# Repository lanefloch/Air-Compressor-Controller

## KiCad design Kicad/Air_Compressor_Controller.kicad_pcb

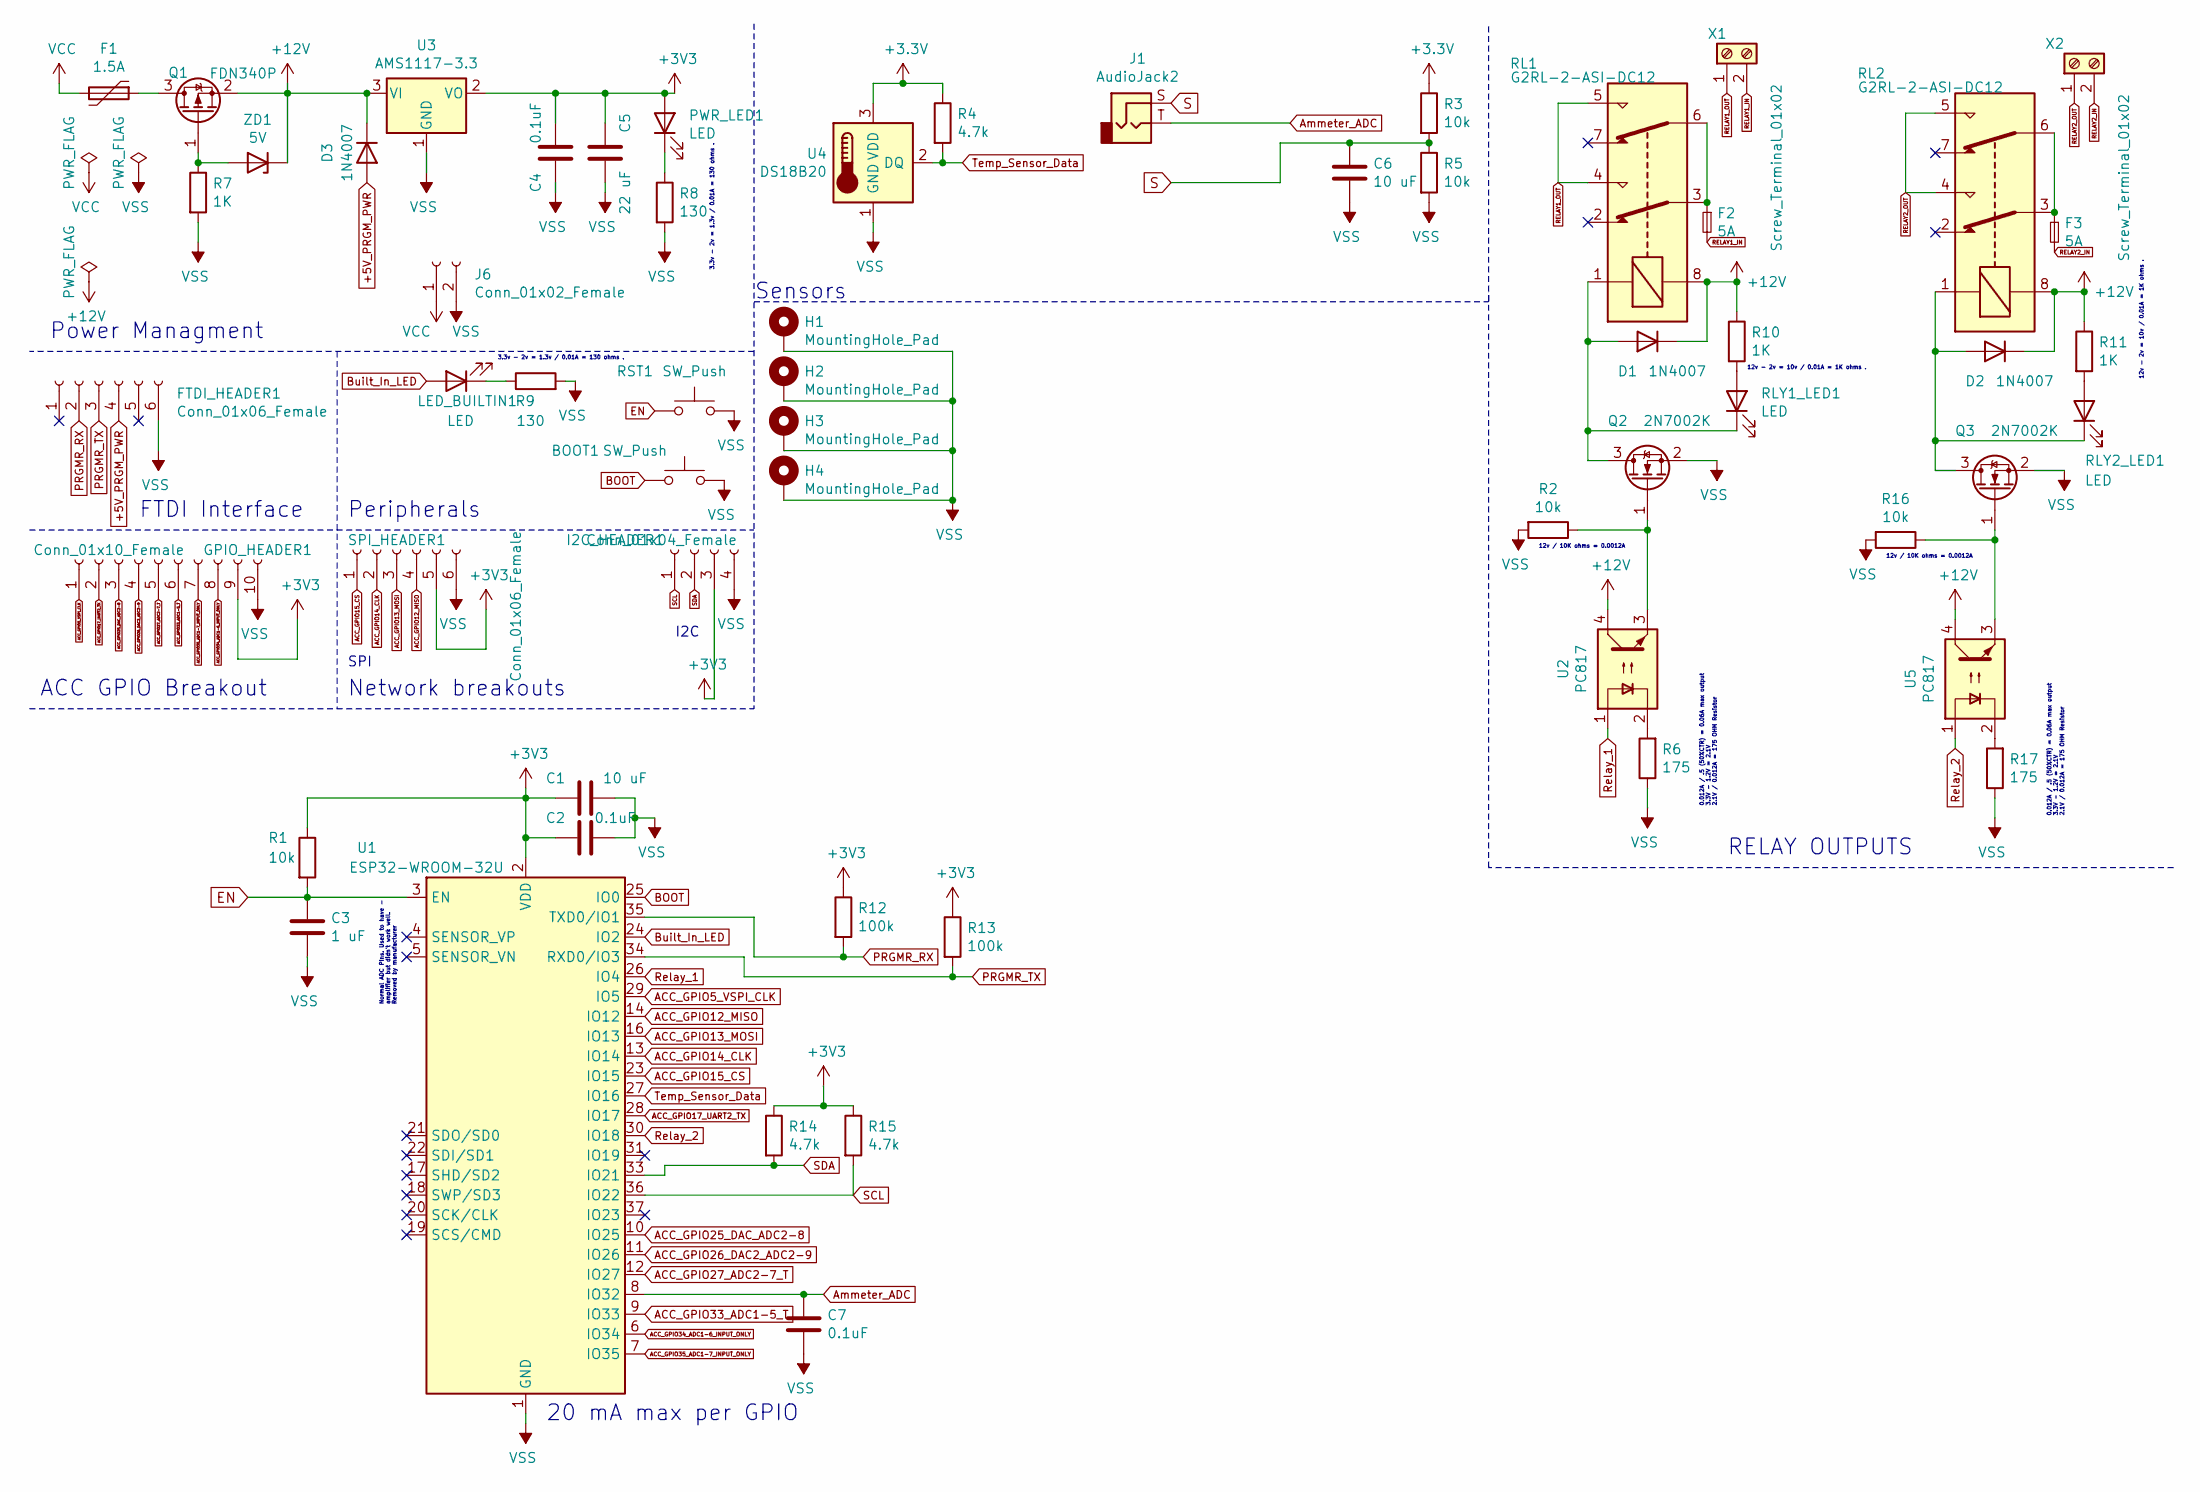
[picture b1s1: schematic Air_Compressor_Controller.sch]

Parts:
BOOT1: SW_Push; SW_SPST_PTS645; LCSC C271750
C1, C6: 10 uF; C_1206_3216Metric_Pad1.33x1.80mm_HandSolder; LCSC C14860
C2, C4, C7: 0.1uF; C_1206_3216Metric_Pad1.33x1.80mm_HandSolder; LCSC C24497
C3: 1 uF; C_1206_3216Metric_Pad1.33x1.80mm_HandSolder; LCSC C1848
C5: 22 uF; C_1206_3216Metric_Pad1.33x1.80mm_HandSolder; LCSC C90146
D1, D2, D3: 1N4007; D_1206_3216Metric_Pad1.42x1.75mm_HandSolder; LCSC C108803
F1: 1.5A; Fuse_1206_3216Metric_Pad1.42x1.75mm_HandSolder; LCSC C883133
F2, F3: 5A; Fuseholder_Cylinder-5x20mm_Stelvio-Kontek_PTF78_Horizontal_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; LCSC C58066
FTDI_HEADER1: Conn_01x06_Female; PinHeader_1x06_P2.54mm_Vertical; LCSC C40877
GPIO_HEADER1: Conn_01x10_Female; PinHeader_1x10_P2.54mm_Vertical; LCSC C35445
H1, H2, H3, H4: MountingHole_Pad; MountingHole_3.2mm_M3_Pad_Via; LCSC N/A
I2C_HEADER1: Conn_01x04_Female; PinHeader_1x04_P2.54mm_Vertical; LCSC C2718488
J1: AudioJack2; Jack_3.5mm_PJ320D_Horizontal; LCSC C521460
J6: Conn_01x02_Female; PinHeader_1x02_P2.54mm_Vertical; LCSC N/A
LED_BUILTIN1: LED; LED_0805_2012Metric_Pad1.15x1.40mm_HandSolder; LCSC C72037
PWR_LED1: LED; LED_0805_2012Metric_Pad1.15x1.40mm_HandSolder; LCSC C72037
Q1: FDN340P; SOT-23; LCSC C2890122
Q2, Q3: 2N7002K; SOT-23; LCSC C38161
R1, R2, R3, R5, R16: 10k; R_1206_3216Metric_Pad1.30x1.75mm_HandSolder; LCSC C140407
R4, R14, R15: 4.7k; R_1206_3216Metric_Pad1.30x1.75mm_HandSolder; LCSC C17936
R6, R17: 175; R_1206_3216Metric_Pad1.30x1.75mm_HandSolder; LCSC C322897
R7, R10, R11: 1K; R_1206_3216Metric_Pad1.30x1.75mm_HandSolder; LCSC C1469
R8, R9: 130; R_1206_3216Metric_Pad1.30x1.75mm_HandSolder; LCSC C17914
R12, R13: 100k; R_1206_3216Metric_Pad1.30x1.75mm_HandSolder; LCSC C118849
RL1, RL2: G2RL-2-ASI-DC12; Relay_DPDT_Omron_G2RL; LCSC C61458
RLY1_LED1, RLY2_LED1: LED; LED_0805_2012Metric_Pad1.15x1.40mm_HandSolder; LCSC C72037
RST1: SW_Push; SW_SPST_PTS645; LCSC C271750
SPI_HEADER1: Conn_01x06_Female; PinHeader_1x06_P2.54mm_Vertical; LCSC C40877
U1: ESP32-WROOM-32U; LCSC C328062
U2, U5: PC817; DIP-4_W7.62mm; LCSC C390734
U3: AMS1117-3.3; SOT-223-3_TabPin2; LCSC C347222
U4: DS18B20; TO-92_Inline; LCSC C376006
X1, X2: Screw_Terminal_01x02; TerminalBlock_Phoenix_MKDS-1,5-2_1x02_P5.00mm_Horizontal; LCSC N/A
ZD1: 5V; D_SOD-323_HandSoldering; LCSC C22612

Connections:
+5V_PRGM_PWR: D3.2 (A), FTDI_HEADER1.4
+12V: D1.1 (K), D2.1 (K), D3.1 (K), Q1.2 (S), R10.1, R11.1, RL1.8, RL2.8, U2.4, U3.3 (VI), U5.4, ZD1.1 (K)
ACC_GPIO5_VSPI_CLK: GPIO_HEADER1.1, U1.29 (IO5)
ACC_GPIO12_MISO: SPI_HEADER1.4, U1.14 (IO12)
ACC_GPIO13_MOSI: SPI_HEADER1.3, U1.16 (IO13)
ACC_GPIO14_CLK: SPI_HEADER1.2, U1.13 (IO14)
ACC_GPIO15_CS: SPI_HEADER1.1, U1.23 (IO15)
ACC_GPIO17_UART2_TX: GPIO_HEADER1.2, U1.28 (IO17)
ACC_GPIO25_DAC_ADC2-8: GPIO_HEADER1.3, U1.10 (IO25)
ACC_GPIO26_DAC2_ADC2-9: GPIO_HEADER1.4, U1.11 (IO26)
ACC_GPIO27_ADC2-7_T: GPIO_HEADER1.5, U1.12 (IO27)
ACC_GPIO33_ADC1-5_T: GPIO_HEADER1.6, U1.9 (IO33)
ACC_GPIO34_ADC1-6_INPUT_ONLY: GPIO_HEADER1.8, U1.6 (IO34)
ACC_GPIO35_ADC1-7_INPUT_ONLY: GPIO_HEADER1.7, U1.7 (IO35)
Ammeter_ADC: C7.1, J1.T, U1.8 (IO32); also elsewhere on the board
BOOT: BOOT1.1, U1.25 (IO0)
Built_In_LED: LED_BUILTIN1.2 (A), U1.24 (IO2)
EN: C3.1, R1.2, RST1.1, U1.3 (EN)
unnamed: D1.2 (A), Q2.3 (D), RL1.1, RLY1_LED1.1 (K)
unnamed: D2.2 (A), Q3.3 (D), RL2.1, RLY2_LED1.1 (K)
unnamed: F1.1, Q1.3 (D)
unnamed: F2.1, RL1.3, RL1.6
unnamed: F3.1, RL2.3, RL2.6
unnamed: LED_BUILTIN1.1 (K), R9.1
unnamed: PWR_LED1.1 (K), R8.1
unnamed: Q1.1 (G), R7.1, ZD1.2 (A)
unnamed: Q2.1 (G), R2.1, U2.3
unnamed: Q3.1 (G), R16.1, U5.3
unnamed: R6.2, U2.2
unnamed: R10.2, RLY1_LED1.2 (A)
unnamed: R11.2, RLY2_LED1.2 (A)
unnamed: R17.2, U5.2
PRGMR_RX: FTDI_HEADER1.2, R12.2, U1.35 (TXD0/IO1)
PRGMR_TX: FTDI_HEADER1.3, R13.2, U1.34 (RXD0/IO3)
RELAY1_IN: F2.2, X1.2
RELAY1_OUT: RL1.4, RL1.5, X1.1
RELAY2_IN: F3.2, X2.2
RELAY2_OUT: RL2.4, RL2.5, X2.1
Relay_1: U1.26 (IO4), U2.1
Relay_2: U1.30 (IO18), U5.1
S: C6.1, J1.S, R3.2, R5.1; also elsewhere on the board
SCL: I2C_HEADER1.1, R15.2, U1.36 (IO22)
SDA: I2C_HEADER1.2, R14.2, U1.33 (IO21)
Temp_Sensor_Data: R4.2, U1.27 (IO16), U4.2 (DQ)
VCC: F1.2, J6.1
VSS: BOOT1.2, C1.1, C2.1, C3.2, C4.2, C5.1, C6.2, C7.2, FTDI_HEADER1.6, GPIO_HEADER1.10, H1.1, H2.1, H3.1, H4.1, I2C_HEADER1.4, J6.2, Q2.2 (S), Q3.2 (S), R2.2, R5.2, R6.1, R7.2, R8.2, R9.2, R16.2, R17.1, RST1.2, SPI_HEADER1.6, U1.1 (GND), U1.15 (GND), U1.38 (GND), U1.39 (GND), U3.1 (GND), U4.1 (GND)

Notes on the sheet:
12v / 10K ohms = 0.0012A
0.012A / .5 (50%CTR) = 0.06A max output 3.3V - 1.2V = 2.1V 2.1V / 0.012A = 175 OHM Resistor
Power Managment
FTDI Interface
Peripherals
3.3v - 2v = 1.3v / 0.01A = 130 ohms .
Normal ADC Pins. Used to have - amplifier but didn't work well. Removed by manufacturer
20 mA max per GPIO
Network breakouts
SPI
I2C
ACC GPIO Breakout
Sensors
12v - 2v = 10v / 0.01A = 1K ohms .
RELAY OUTPUTS

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
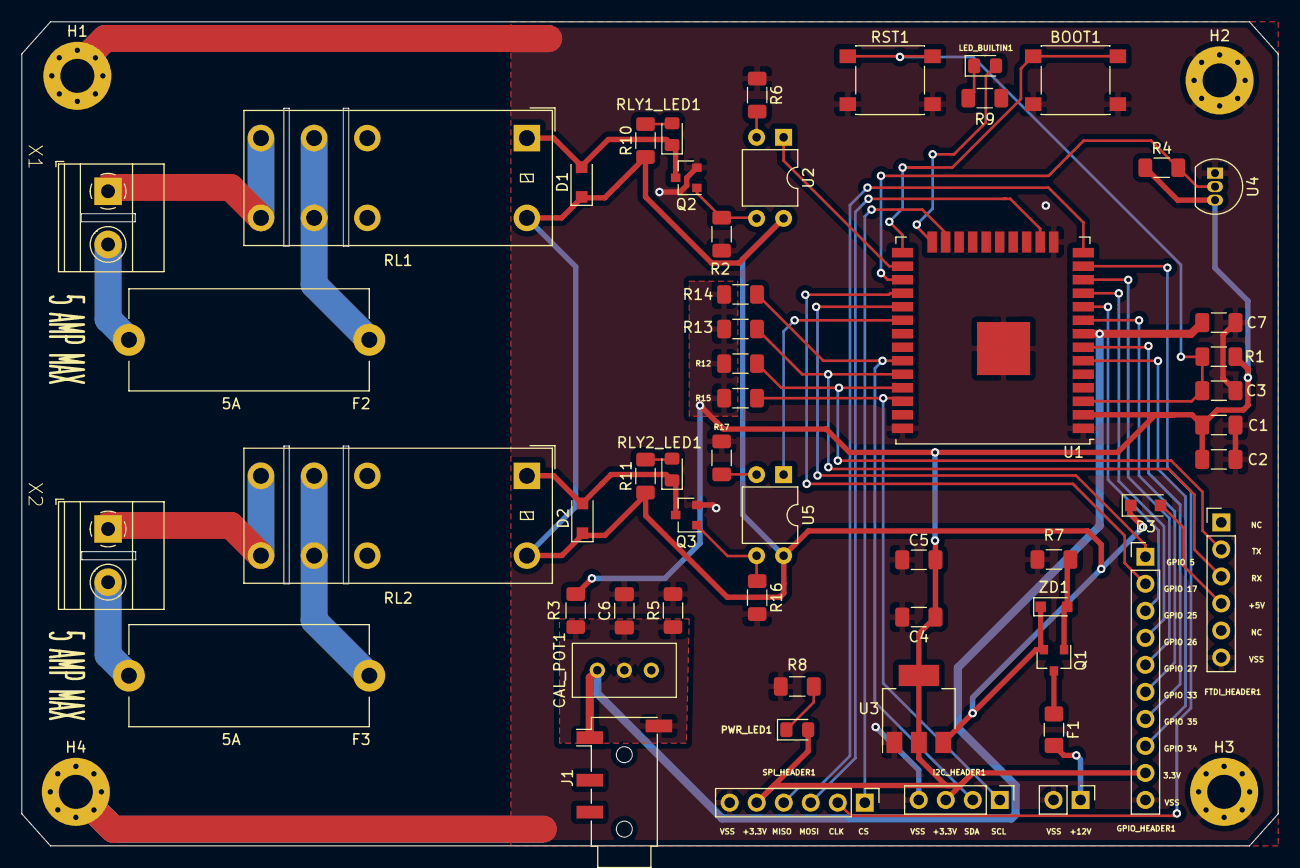
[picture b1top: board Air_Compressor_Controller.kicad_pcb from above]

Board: 2 copper layers, 118.1 x 77.5 mm, 60 parts (0 on the bottom side), 47 nets.

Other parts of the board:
CAL_POT1: 5k; Potentiometer_Bourns_3296W_Vertical

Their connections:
Ammeter_ADC: CAL_POT1.3; also elsewhere on the board
S: CAL_POT1.2; also elsewhere on the board

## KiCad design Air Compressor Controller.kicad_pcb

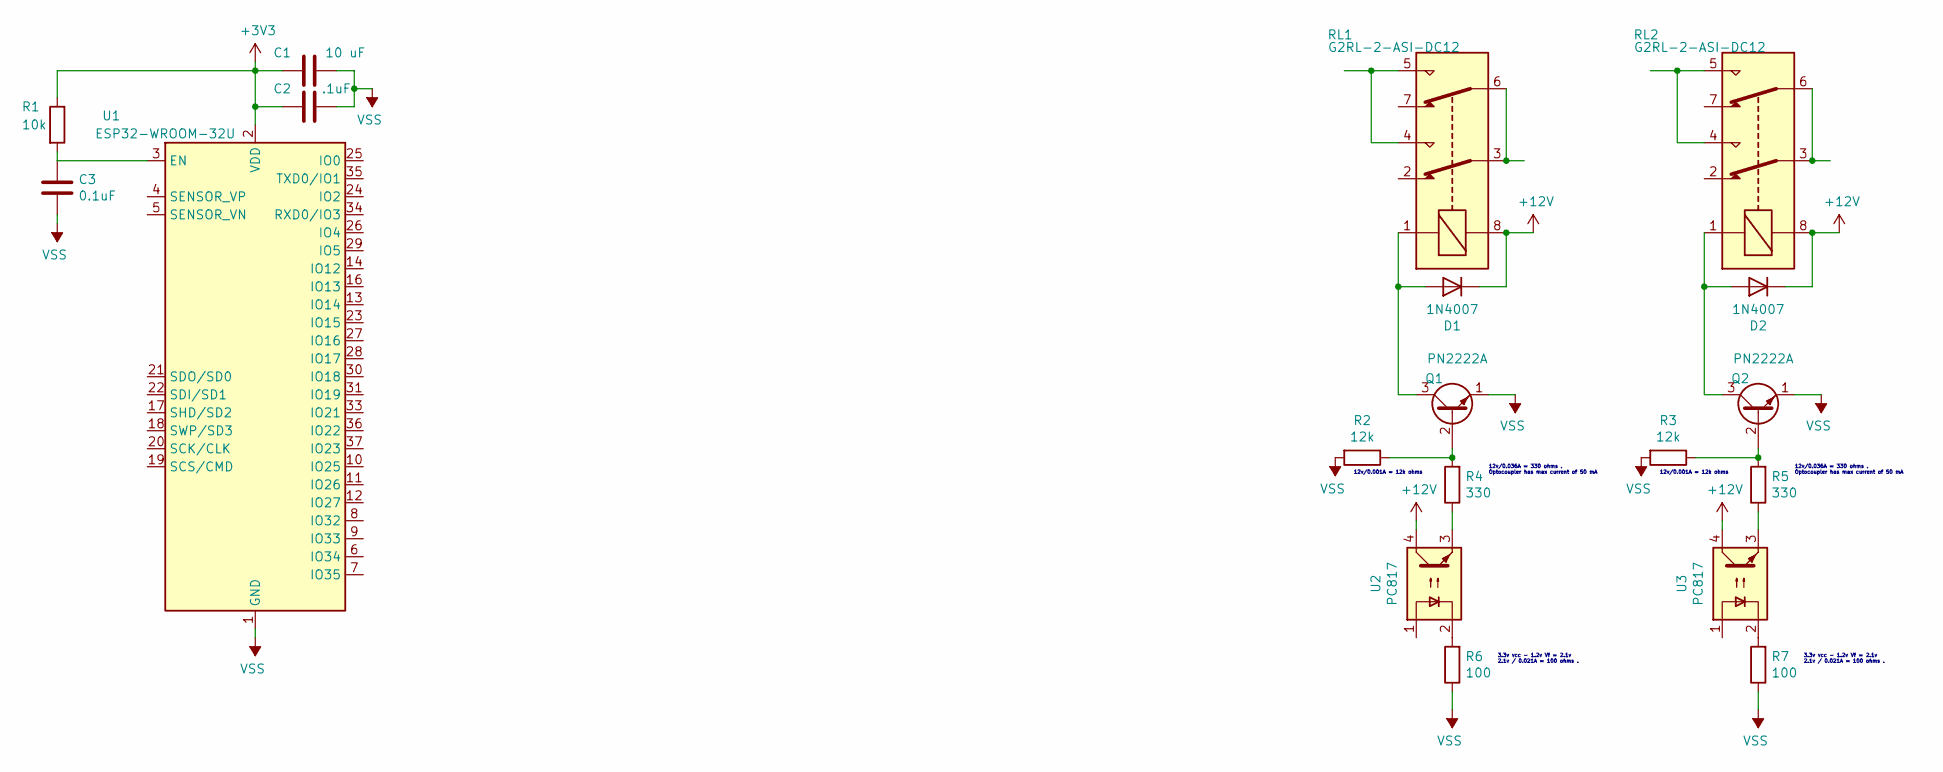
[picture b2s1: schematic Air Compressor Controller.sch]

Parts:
C1: 10 uF; C_1206_3216Metric_Pad1.33x1.80mm_HandSolder
C2: .1uF; C_1206_3216Metric_Pad1.33x1.80mm_HandSolder
C3: 0.1uF; C_1206_3216Metric_Pad1.33x1.80mm_HandSolder
D1, D2: 1N4007; D_1206_3216Metric_Pad1.42x1.75mm_HandSolder
Q1, Q2: PN2222A; TO-92_Inline
R1: 10k; R_1206_3216Metric_Pad1.30x1.75mm_HandSolder
R2, R3: 12k; R_1206_3216Metric_Pad1.30x1.75mm_HandSolder
R4, R5: 330; R_1206_3216Metric_Pad1.30x1.75mm_HandSolder
R6, R7: 100; R_1206_3216Metric_Pad1.30x1.75mm_HandSolder
RL1, RL2: G2RL-2-ASI-DC12; Relay_DPDT_Omron_G2RL
U1: ESP32-WROOM-32U
U2, U3: PC817; DIP-4_W7.62mm

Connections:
+3V3: C1.2, C2.2, R1.1, U1.2 (VDD)
+12V: D1.1 (K), D2.1 (K), RL1.8, RL2.8, U2.4, U3.4
unnamed: C3.1, R1.2, U1.3 (EN)
unnamed: D1.2 (A), Q1.3 (C), RL1.1
unnamed: D2.2 (A), Q2.3 (C), RL2.1
unnamed: Q1.2 (B), R2.1, R4.2
unnamed: Q2.2 (B), R3.1, R5.2
unnamed: R4.1, U2.3
unnamed: R5.1, U3.3
unnamed: R6.2, U2.2
unnamed: R7.2, U3.2
unnamed: RL1.3, RL1.6
unnamed: RL1.4, RL1.5
unnamed: RL2.3, RL2.6
unnamed: RL2.4, RL2.5
VSS: C1.1, C2.1, C3.2, Q1.1 (E), Q2.1 (E), R2.2, R3.2, R6.1, R7.1, U1.1 (GND), U1.15 (GND), U1.38 (GND), U1.39 (GND)

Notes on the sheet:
12v/0.001A = 12k ohms
12v/0.036A = 330 ohms . Optocoupler has max current of 50 mA
3.3v vcc - 1.2v Vf = 2.1v 2.1v / 0.021A = 100 ohms .

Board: 2 copper layers, 19 parts (0 on the bottom side), 16 nets, no tracks yet.

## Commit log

2022-06-01 Init
2022-07-12 update 7/11/22
2022-07-12 2nd update 7/11/22
